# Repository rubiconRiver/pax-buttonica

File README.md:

# Pax Buttonica

Big glowing turn buttons for Twilight Imperium 4 — a web app that runs the table, plus an open standard for the physical buttons. (Working title. Unofficial fan project; not affiliated with Fantasy Flight Games or Asmodee.)

**Status:** the web app is playable today — with simulated on-screen buttons, or with **phones as buttons**. Firmware for real buttons is written and compiles, but no hardware has been built yet.

## Run it

```bash
npm install
npm run dev
```

| Route | What |
|---|---|
| `/` | Landing page: the pitch, a self-playing table, how it's wired |
| `/demo` | Interactive demo with a guided tour and the **scenario lab** (jump to any situation) |
| `/play` | A real game: setup, profiles, seat claiming. Survives a page reload |
| `/me` | Set up your own profile (name, colour, entrance and exit sounds) at home, no game needed |
| `/join` | A phone becomes a button: scan the QR from the *Phones* menu (setup screen or in a game), or type the room code. Players say who they are and edit their own profile and sounds from there |
| `/button` | Concept drawings of the physical button: exploded view, size, target dimensions. Made for sharing |
| `/parts` | Interactive shopping list: pick how many buttons and what you already own, tick things off, read what each part is for |
| *(in a game)* **Scoreboard** | Objectives with their requirements, who has scored what, secrets, other points, laws. Opens by itself in the status phase; `B` toggles it. Every phone gets it read-only under "The table" |
| `/bench` | Hardware test bench: connect the USB hub and poke real buttons one at a time |
| `/standard` | The button standard, rendered from `docs/BUTTON_STANDARD.md` |

Number keys `1`–`8` are the on-screen buttons: tap a key to tap, double-press to play a strategy card, hold it to end the turn. `⌘Z` undoes.

```bash
npm test        # rules engine tests
npm run build   # typecheck + production build (deploys to Vercel as a static site)
```

## How it fits together

```
src/engine/     Pure rules. reduce(state, action) → state; deriveOutputs(state) → one light per seat.
src/hardware/   The wire protocol, and the Web Serial transport to the USB hub (untested — no hardware yet).
api/            Vercel functions: profiles and uploaded clips in Neon Postgres (DATABASE_URL). No auth yet.
src/remote/     The game's copy on the site (api/game.ts) and the phones' inbox (api/actions.ts). Host writes, phones read and post.
firmware/       ESP32-C3 sketches for the hub and the buttons. See docs/HARDWARE.md.
hardware/pcb/   The button's carrier board: generator script, KiCad file, renders and the zip a board house needs.
src/audio/      WebAudio synth: interface sounds, jingles as note lists, uploaded clips (IndexedDB).
src/components/ Device.tsx is the simulated button; components/game/ is the table.
src/state/      Tiny stores: game (+undo, persisted), settings, profiles, demo seeding.
docs/           BUTTON_STANDARD.md — the spec. HARDWARE.md — parts, wiring, flashing, bring-up. SHOPPING.md — the cart.
```

The important idea: **buttons are dumb.** They show the colour and mode they're told to and report `tap` / `double` / `hold`. Every rule lives in `src/engine`, so the simulator and real hardware can't drift apart — they're fed by the same function.

## Helping out

See the "Help wanted" section on the landing page, and the open questions at the bottom of the standard.

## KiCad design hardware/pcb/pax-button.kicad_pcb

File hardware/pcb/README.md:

# The button's carrier board

A 70 mm round, two-layer board that every part of a button solders onto, so the only loose wires left are three to the LED ring and two to the batteries.

**Revision 0.2. Status: designed, rule-checked, never manufactured.** (v0.1, the first one ordered, is the same board without R2/R3 and the number box, and with C1 nearer the middle; it works the same.) KiCad's design-rule check passes with no violations and nothing unconnected. No board has been made, and the ESP32 module's footprint was drawn from published dimensions, not from a module in hand. Order a small batch and test one before building six.

## What's on it

| Ref | Part | Notes |
|---|---|---|
| U1 | ESP32-C3 SuperMini | Top of the board, USB-C at the rim. A **spare solder hole sits beside every pin**, so anything the module can do is reachable later: extra buttons, a speaker amp, battery sensing. |
| SW1 | MX-style keyboard switch | Dead centre. Any Cherry-MX-compatible switch, 3-pin or 5-pin. One side to ground, the other to the 5th pin on the module's power side. |
| J1 | Battery, 4 × AA NiMH | A 5.08 mm screw terminal, or just solder the holder's leads into the holes. **+ is on the left.** |
| D1 | 1N5817 diode | Reverse-polarity protection. Stripe to the right (marked K). |
| C1 | 1000 µF capacitor | Near the rim, below the LED connector, where it clears both the 8-LED and the 50 mm 12-LED ring. Stripe (negative) away from the + mark. |
| R2, R3 | 100 kΩ × 2, optional | A battery gauge: they halve the battery voltage for the ESP32 to read. Fit both and set `BATTERY_PIN` in the firmware (the fourth pin on the 5V side, usually 4); the test bench and the game then show each button's battery. Leave them off and nothing changes. |
| J2 | LED ring | 5V · DIN · G. Solder the ring's three wires straight in, or fit a pin header. |
| R1 / JP1 | 330 Ω, optional | JP1 is a jumper that is *already bridged* on the bare board, so with R1 left empty everything works. To use the resistor: fit R1 and cut the thin link between JP1's two pads. |
| J3 | Three ground holes | For the other leg of any extra buttons. |
| H1–H4 | M3 mounting holes | On a 46 × 38 mm rectangle. |
| Back | "No." box | Somewhere to write which button this is. |

The ground is a copper pour on both sides. There is no copper under the module's antenna.

## Two things the board deliberately does not assume

1. **Which way the module's GPIO numbers run.** Sources disagree on whether the five pins after 3V3 are labelled 4-3-2-1-0 or 0-1-2-3-4. The switch goes to the **fifth pin on the 5V side**. Read the number printed beside that pin on your module and put it in `firmware/button/config.h` as the first entry of `BUTTON_PINS`. The LED data line goes to GPIO10, which everyone agrees on.
2. **That your module isn't mirrored.** Looking down on the module with USB-C at the top, 5V should be the top pin on the **right**. If yours has 5V on the left, solder the module to the **back** of the board instead; flipping it swaps the rows back. Check before you solder: it's printed on both sides of the board too.

## Assembly

Step by step in [`docs/HARDWARE.md`](../../docs/HARDWARE.md#putting-a-button-together-on-the-board): diode, ESP32 (on its pin strips, USB off the edge), switch, capacitor, battery leads, LED ring.

## Ordering (JLCPCB, PCBWay and similar)

Upload `pax-button-v0.2-gerbers.zip`. The preview should show a round board with a square switch outline in the middle. Then:

- 2 layers · 70 × 70 mm · quantity 5 or 10 (usually the same price)
- 1.6 mm thick · **green** solder mask (other colours can add days) · HASL finish · 1 oz copper
- Fastest courier they offer (DHL Express or similar). Expect duty, GST and a brokerage fee at the door.

## Regenerating it

The whole board is produced by a script, so changes are reviewable text:

```bash
/Applications/KiCad/KiCad.app/Contents/Frameworks/Python.framework/Versions/Current/bin/python3 make_board.py
kicad-cli pcb drc pax-button.kicad_pcb
```

`pax-button.kicad_pcb` opens in KiCad 9 or later if you would rather edit it by hand.

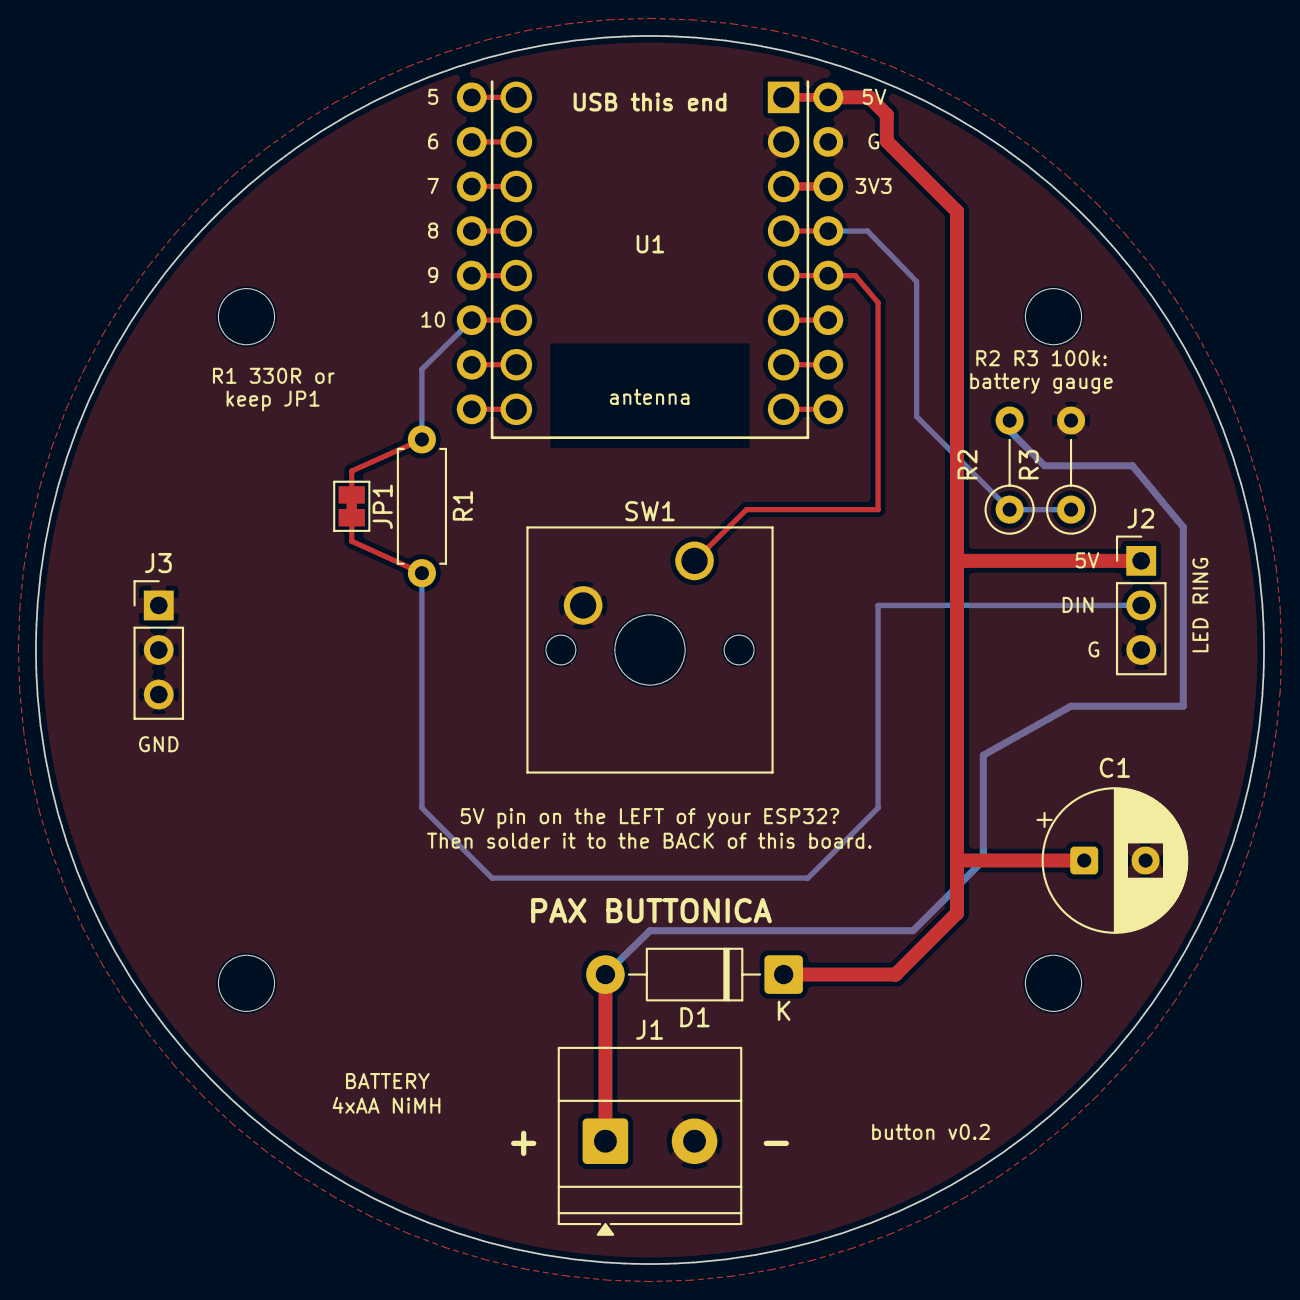
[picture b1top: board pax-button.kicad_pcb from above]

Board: 2 copper layers, 70.0 x 70.0 mm, 15 parts (0 on the bottom side), 18 nets.

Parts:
C1: 1000uF 16V; CP_Radial_D8.0mm_P3.50mm
D1: 1N5817; D_DO-41_SOD81_P10.16mm_Horizontal
H1, H2, H3, H4: MountingHole_3.2mm_M3
J1: BATTERY 4xAA NiMH; TerminalBlock_Phoenix_MKDS-1,5-2-5.08_1x02_P5.08mm_Horizont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
J2: LED RING; PinHeader_1x03_P2.54mm_Vertical
J3: GND x3; PinHeader_1x03_P2.54mm_Vertical
JP1: bypass R1; SolderJumper-2_P1.3mm_Bridged_Pad1.0x1.5mm
R1: 330R (optional); R_Axial_DIN0207_L6.3mm_D2.5mm_P7.62mm_Horizontal
R2, R3: 100k (optional); R_Axial_DIN0207_L6.3mm_D2.5mm_P5.08mm_Vertical
SW1: MX switch; SW_Cherry_MX_1.00u_PCB
U1: ESP32-C3 SuperMini

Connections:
+3V3: U1.R3, U1.RB3
+5V: C1.1, D1.1, J2.1, U1.R1, U1.RB1
GND: C1.2, J1.2, J2.3, J3.1, J3.2, J3.3, R3.2, SW1.2, U1.R2, U1.RB2
IO5: U1.L1, U1.LB1
IO6: U1.L2, U1.LB2
IO7: U1.L3, U1.LB3
IO8: U1.L4, U1.LB4
IO9: U1.L5, U1.LB5
IO_C: U1.R6, U1.RB6
IO_D: U1.R7, U1.RB7
IO_E: U1.R8, U1.RB8
LED_DIN: J2.2, JP1.2, R1.2
LED_MCU: JP1.1, R1.1, U1.L6, U1.LB6
SW_MAIN: SW1.1, U1.R5, U1.RB5
UART_A: U1.L7, U1.LB7
UART_B: U1.L8, U1.LB8
VBAT: D1.2, J1.1, R2.2
VSENSE: R2.1, R3.1, U1.R4, U1.RB4
